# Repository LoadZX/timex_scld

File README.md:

# Timex SCLD

This is an implementation of the Timex TC2068 SCLD as can be found in Timex models TC2048 and TC2068.

# License

All the design files (VHDL code, PCB designs) are licensed under a Creative Commons Attribution-ShareAlike 4.0 International License.

You should have received a copy of the license along with this work. If not, see <https://creativecommons.org/licenses/by-sa/4.0/>.

A copy of the legal license text is placed in this repository (see LICENSE)

# Trademarks

TIMEX is a trademark of TIMEX GROUP USA, INC

The authors of this work are not affiliated, sponsored or have any partnership with the trademark holders. The trademark holders do not sponsor or endorse this work or any of its authors.

Xilinx is a registered trademark of Xilinx in the United States and other countries.

# Implementation code
The implementation (VHDL code and associated files) target a XC95144XL-10TQ100 CPLD from Xilinx. 

## Synthesis
The tool used for synthesis and fitting was Xilinx ISE 14.7. 

## Programming
Programming can be acomplished with Xilinx Impact using a proper programmer (i.e., Xilinx Platform Cable)

# Building

Just type "make" under the SDLC implementation folder (syn/xilinx). Alternatively you can try loading the ISE project in the same directory.

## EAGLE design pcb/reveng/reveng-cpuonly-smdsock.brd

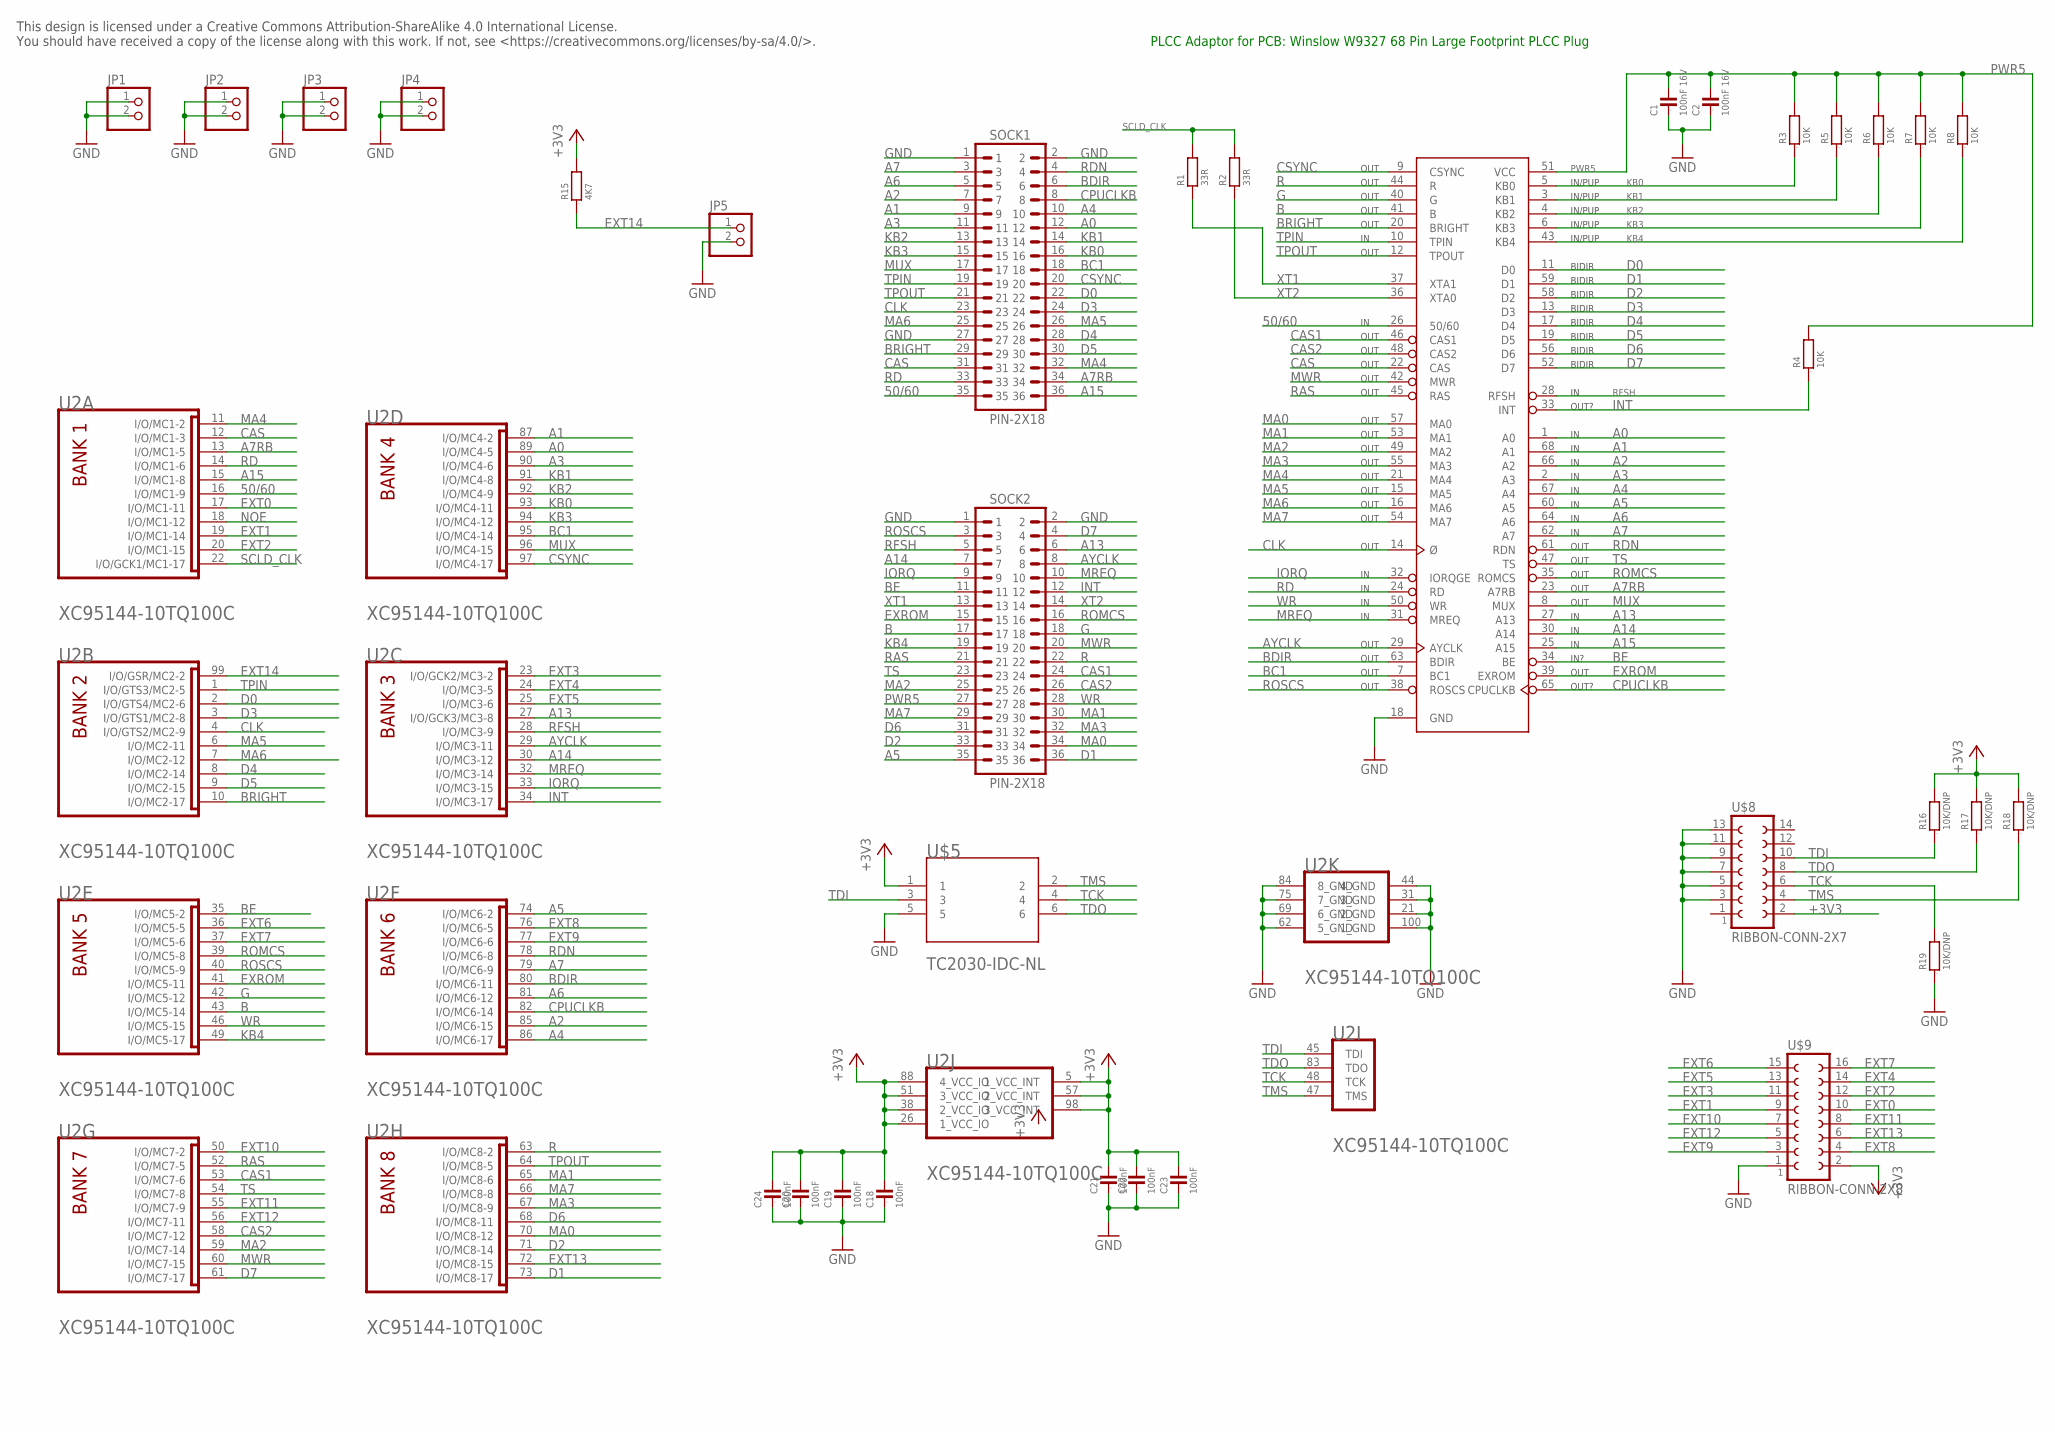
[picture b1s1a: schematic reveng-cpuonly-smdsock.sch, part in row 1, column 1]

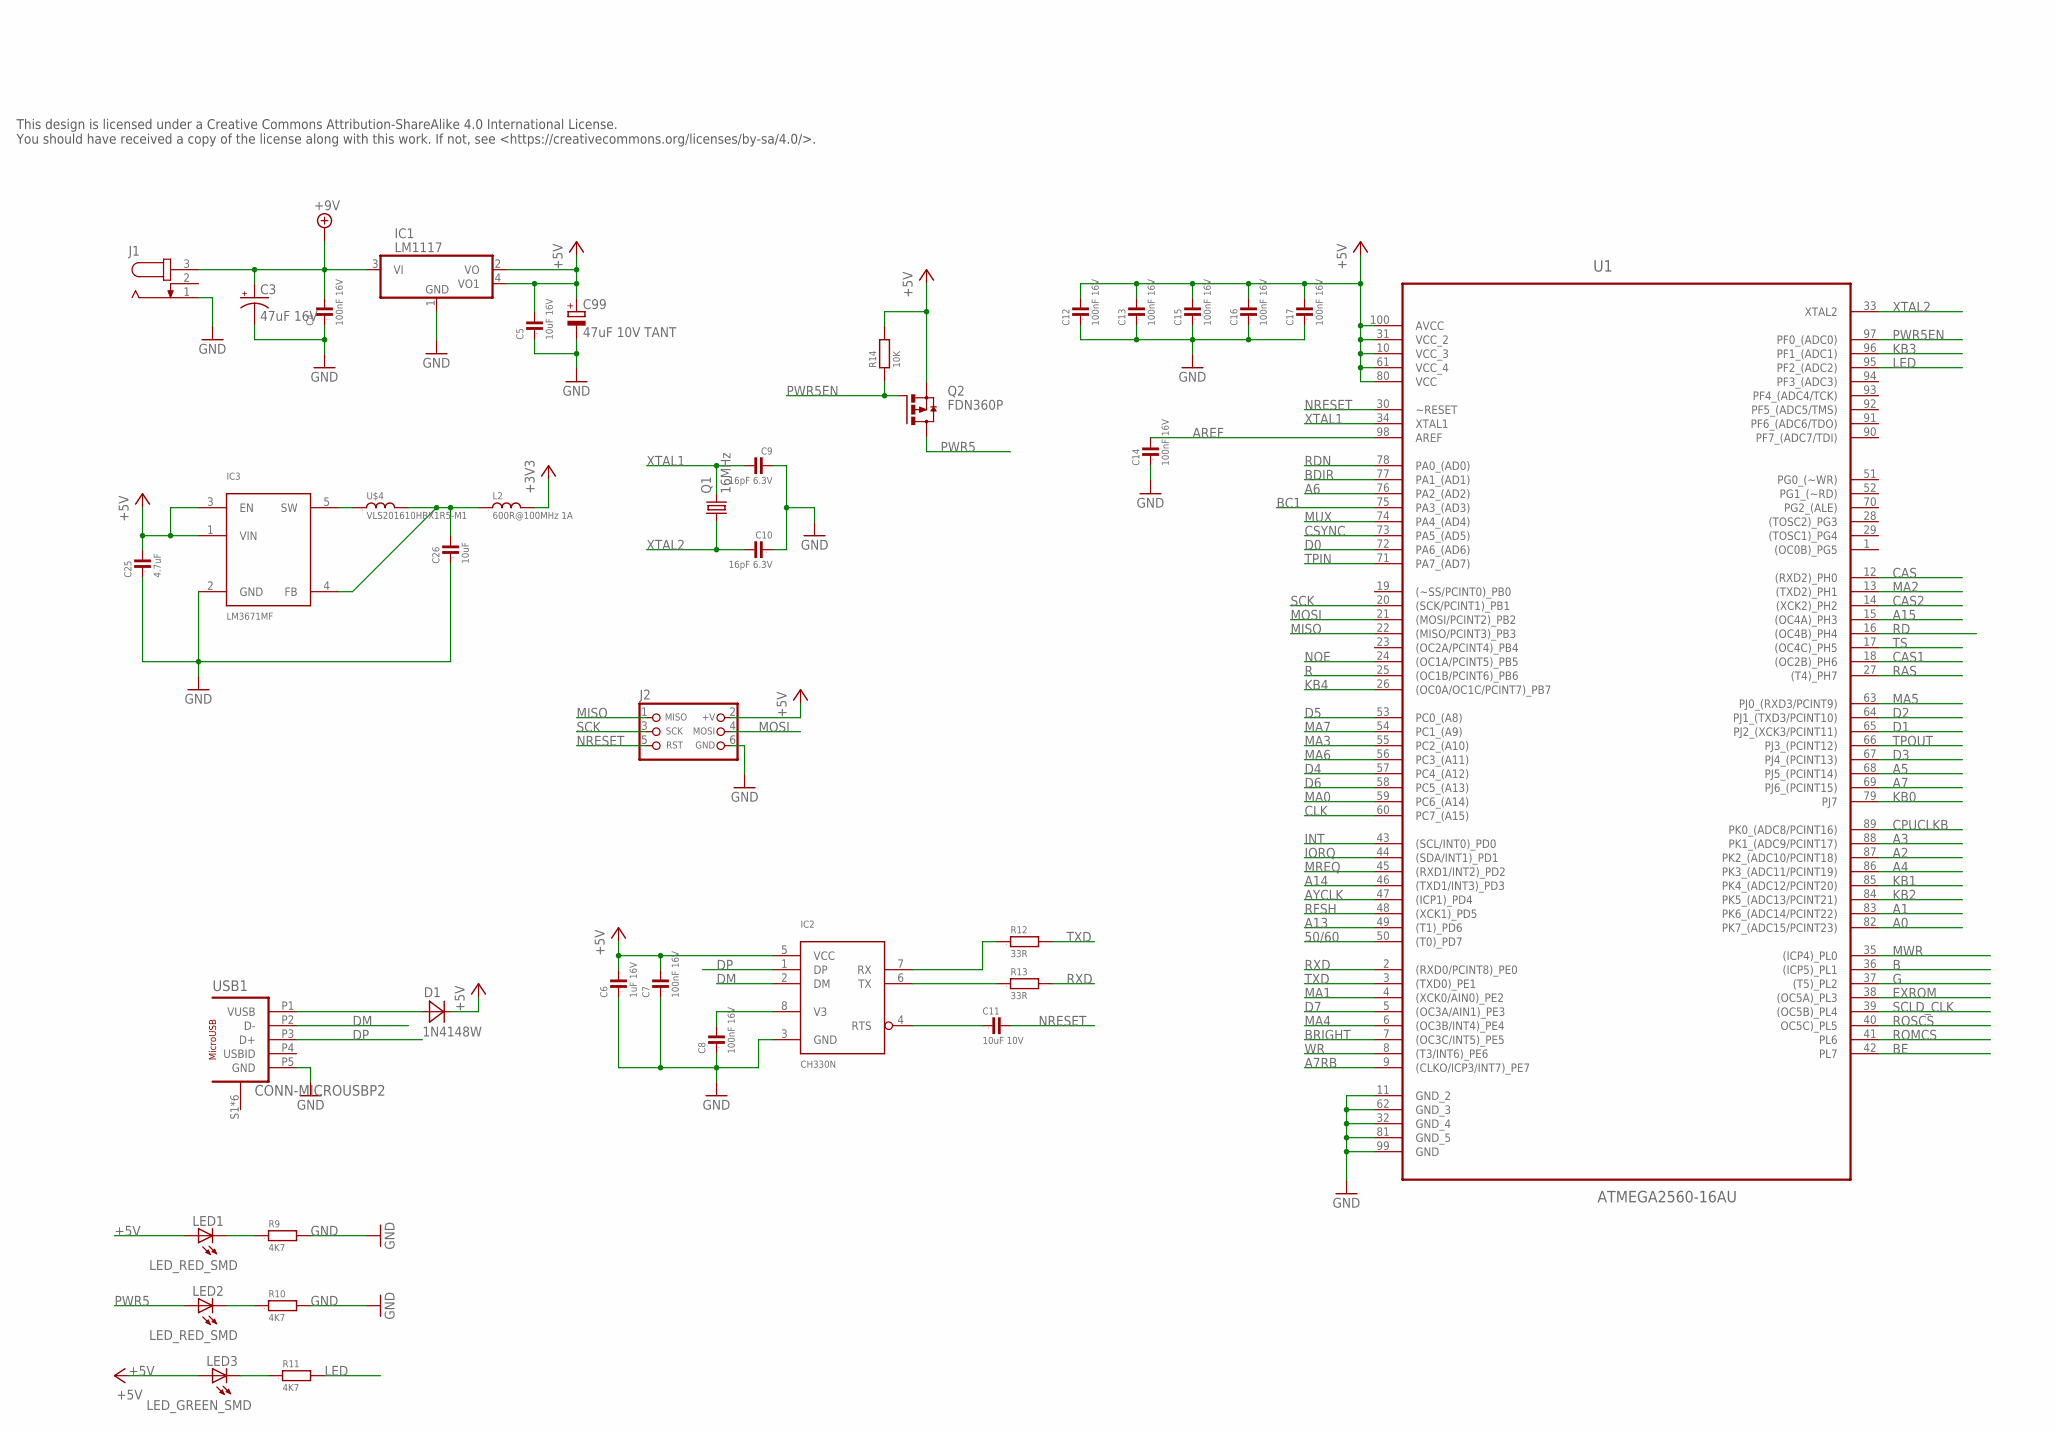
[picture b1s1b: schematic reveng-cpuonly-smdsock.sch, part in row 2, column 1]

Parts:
C1, C2, C4, C7, C8, C12, C13, C14, C15, C16, C17: 100nF 16V; 0603
C3: 47uF 16V; E2,5-6
C5: 10uF 16V; 0805
C6: 1uF 16V; 0603
C9, C10: 16pF 6.3V; 0603
C11: 10uF 10V; 0603
C18, C19, C20, C21, C22, C23, C24: 100nF; 0603
C25: 4.7uF; 0805
C26: 10uF; 0805
C99: 47uF 10V TANT; TANT_CASE_A
D1: 1N4148W; SOD-123
IC1: LM1117; SOT223
IC2: CH330N; SOIC8
IC3: LM3671MF; SOT23-5L
J1: JACK-PLUG; SPC4078-NOSLOT
J2: CON_HEADER_PRG_AVR_ICSP-PTH; HEADER_PRG_2X03
JP1, JP2, JP3, JP4, JP5: PINHD-1X2; 1X02
L2: 600R@100MHz 1A; 0805
LED1, LED2: LED_RED_SMD; LED-603
LED3: LED_GREEN_SMD; LED-603
Q1: 16MHz; HC49U-V
Q2: FDN360P; SUPER-SOT3
R1, R2, R12, R13: 33R; 0603
R3, R4, R5, R6, R7, R8, R14: 10K; 0603
R9, R10, R11, R15: 4K7; 0603
R16, R17, R18, R19: 10K/DNP; 0603
SCLD1: 2048SCLDSMDSOCK; PLCC68-AMP-SOCKET
SOCK1, SOCK2: PIN-2X18
U1: ATMEGA2560-16AU; QFP50P1600X1600X120-100N
U2: XILINX_XC95144-10TQ100CLQFP; LQFP100
U$4: VLS201610HBX1R5-M1; IND_0806
U$5: TC2030-IDC-NL
U$8: RIBBON-CONN-2X7
U$9: RIBBON-CONN-2X8
USB1: CONN-MICROUSBP2; MICROUSB_SMD_TH_7.5MM_4.85MM

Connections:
50/60: SCLD1.26 (50/60), SOCK1.35, U1.50 ((T0)_PD7), U2.16 (I/O/MC1-9)
+3V3: C18.2, C19.2, C20.2, C21.2, C22.2, C23.2, C24.2, L2.2, R15.2, R16.2, R17.2, R18.2, U2.5 (1_VCC_INT), U2.26 (1_VCC_IO), U2.38 (2_VCC_IO), U2.51 (3_VCC_IO), U2.57 (2_VCC_INT), U2.88 (4_VCC_IO), U2.98 (3_VCC_INT), U$5.1, U$8.2, U$9.2
+5V: C5.2, C6.2, C7.2, C12.2, C13.2, C15.2, C16.2, C17.2, C25.2, C99.PLUS (+), D1.1 (C), IC1.2 (VO), IC1.4 (VO1), IC2.5 (VCC), IC3.1 (VIN), IC3.3 (EN), J2.2 (+V), LED1.A, LED3.A, Q2.2 (S), R14.2, U1.10 (VCC_3), U1.31 (VCC_2), U1.61 (VCC_4), U1.80 (VCC), U1.100 (AVCC)
+9V: C3.+, C4.2, IC1.3 (VI), J1.3
A0: SCLD1.1 (A0), SOCK1.12, U1.82 (PK7_(ADC15/PCINT23)), U2.89 (I/O/MC4-5)
A1: SCLD1.68 (A1), SOCK1.9, U1.83 (PK6_(ADC14/PCINT22)), U2.87 (I/O/MC4-2)
A2: SCLD1.66 (A2), SOCK1.7, U1.87 (PK2_(ADC10/PCINT18)), U2.85 (I/O/MC6-15)
A3: SCLD1.2 (A3), SOCK1.11, U1.88 (PK1_(ADC9/PCINT17)), U2.90 (I/O/MC4-6)
A4: SCLD1.67 (A4), SOCK1.10, U1.86 (PK3_(ADC11/PCINT19)), U2.86 (I/O/MC6-17)
A5: SCLD1.60 (A5), SOCK2.35, U1.68 (PJ5_(PCINT14)), U2.74 (I/O/MC6-2)
A6: SCLD1.64 (A6), SOCK1.5, U1.76 (PA2_(AD2)), U2.81 (I/O/MC6-12)
A7: SCLD1.62 (A7), SOCK1.3, U1.69 (PJ6_(PCINT15)), U2.79 (I/O/MC6-9)
A7RB: SCLD1.23 (A7RB), SOCK1.34, U1.9 ((CLKO/ICP3/INT7)_PE7), U2.13 (I/O/MC1-5)
A13: SCLD1.27 (A13), SOCK2.6, U1.49 ((T1)_PD6), U2.27 (I/O/GCK3/MC3-8)
A14: SCLD1.30 (A14), SOCK2.7, U1.46 ((TXD1/INT3)_PD3), U2.30 (I/O/MC3-12)
A15: SCLD1.25 (A15), SOCK1.36, U1.15 ((OC4A)_PH3), U2.15 (I/O/MC1-8)
AREF: C14.2, U1.98 (AREF)
AYCLK: SCLD1.29 (AYCLK), SOCK2.8, U1.47 ((ICP1)_PD4), U2.29 (I/O/MC3-11)
B: SCLD1.41 (B), SOCK2.17, U1.36 ((ICP5)_PL1), U2.43 (I/O/MC5-14)
BC1: SCLD1.7 (BC1), SOCK1.18, U1.75 (PA3_(AD3)), U2.95 (I/O/MC4-14)
BDIR: SCLD1.63 (BDIR), SOCK1.6, U1.77 (PA1_(AD1)), U2.80 (I/O/MC6-11)
BE: SCLD1.34 (BE), SOCK2.11, U1.42 (PL7), U2.35 (I/O/MC5-2)
BRIGHT: SCLD1.20 (BRIGHT), SOCK1.29, U1.7 ((OC3C/INT5)_PE5), U2.10 (I/O/MC2-17)
CAS: SCLD1.22 (CAS), SOCK1.31, U1.12 ((RXD2)_PH0), U2.12 (I/O/MC1-3)
CAS1: SCLD1.46 (CAS1), SOCK2.24, U1.18 ((OC2B)_PH6), U2.53 (I/O/MC7-6)
CAS2: SCLD1.48 (CAS2), SOCK2.26, U1.14 ((XCK2)_PH2), U2.58 (I/O/MC7-12)
CLK: SCLD1.14 (Ø), SOCK1.23, U1.60 (PC7_(A15)), U2.4 (I/O/GTS2/MC2-9)
CPUCLKB: SCLD1.65 (CPUCLKB), SOCK1.8, U1.89 (PK0_(ADC8/PCINT16)), U2.82 (I/O/MC6-14)
CSYNC: SCLD1.9 (CSYNC), SOCK1.20, U1.73 (PA5_(AD5)), U2.97 (I/O/MC4-17)
D0: SCLD1.11 (D0), SOCK1.22, U1.72 (PA6_(AD6)), U2.2 (I/O/GTS4/MC2-6)
D1: SCLD1.59 (D1), SOCK2.36, U1.65 (PJ2_(XCK3/PCINT11)), U2.73 (I/O/MC8-17)
D2: SCLD1.58 (D2), SOCK2.33, U1.64 (PJ1_(TXD3/PCINT10)), U2.71 (I/O/MC8-14)
D3: SCLD1.13 (D3), SOCK1.24, U1.67 (PJ4_(PCINT13)), U2.3 (I/O/GTS1/MC2-8)
D4: SCLD1.17 (D4), SOCK1.28, U1.57 (PC4_(A12)), U2.8 (I/O/MC2-14)
D5: SCLD1.19 (D5), SOCK1.30, U1.53 (PC0_(A8)), U2.9 (I/O/MC2-15)
D6: SCLD1.56 (D6), SOCK2.31, U1.58 (PC5_(A13)), U2.68 (I/O/MC8-11)
D7: SCLD1.52 (D7), SOCK2.4, U1.5 ((OC3A/AIN1)_PE3), U2.61 (I/O/MC7-17)
DM: IC2.2 (DM), USB1.P2 (D-)
DP: IC2.1 (DP), USB1.P3 (D+)
EXROM: SCLD1.39 (EXROM), SOCK2.15, U1.38 ((OC5A)_PL3), U2.41 (I/O/MC5-11)
EXT0: U2.17 (I/O/MC1-11), U$9.10
EXT1: U2.19 (I/O/MC1-14), U$9.9
EXT2: U2.20 (I/O/MC1-15), U$9.12
EXT3: U2.23 (I/O/GCK2/MC3-2), U$9.11
EXT4: U2.24 (I/O/MC3-5), U$9.14
EXT5: U2.25 (I/O/MC3-6), U$9.13
EXT6: U2.36 (I/O/MC5-5), U$9.15
EXT7: U2.37 (I/O/MC5-6), U$9.16
EXT8: U2.76 (I/O/MC6-5), U$9.4
EXT9: U2.77 (I/O/MC6-6), U$9.3
EXT10: U2.50 (I/O/MC7-2), U$9.7
EXT11: U2.55 (I/O/MC7-9), U$9.8
EXT12: U2.56 (I/O/MC7-11), U$9.5
EXT13: U2.72 (I/O/MC8-15), U$9.6
EXT14: JP5.1, R15.1, U2.99 (I/O/GSR/MC2-2)
G: SCLD1.40 (G), SOCK2.18, U1.37 ((T5)_PL2), U2.42 (I/O/MC5-12)
GND: C1.1, C2.1, C3.-, C4.1, C5.1, C6.1, C7.1, C8.1, C9.1, C10.1, C12.1, C13.1, C14.1, C15.1, C16.1, C17.1, C18.1, C19.1, C20.1, C21.1, C22.1, C23.1, C24.1, C25.1, C26.1, C99.MINUS (-), IC1.1 (GND), IC2.3 (GND), IC3.2 (GND), J1.1, J2.6 (GND), JP1.1, JP1.2, JP2.1, JP2.2, JP3.1, JP3.2, JP4.1, JP4.2, JP5.2, R9.2, R10.2, R19.1, SCLD1.18 (GND), SOCK1.1, SOCK1.2, SOCK1.27, SOCK2.1, SOCK2.2, U1.11 (GND_2), U1.32 (GND_4), U1.62 (GND_3), U1.81 (GND_5), U1.99 (GND), U2.21 (2_GND), U2.31 (3_GND), U2.44 (4_GND), U2.62 (5_GND), U2.69 (6_GND), U2.75 (7_GND), U2.84 (8_GND), U2.100 (1_GND), U$5.5, U$8.3, U$8.5, U$8.7, U$8.9, U$8.11, U$8.13, U$9.1, USB1.P5 (GND)
INT: R4.1, SCLD1.33 (INT), SOCK2.12, U1.43 ((SCL/INT0)_PD0), U2.34 (I/O/MC3-17)
IORQ: SCLD1.32 (IORQGE), SOCK2.9, U1.44 ((SDA/INT1)_PD1), U2.33 (I/O/MC3-15)
KB0: R3.1, SCLD1.5 (KB0), SOCK1.16, U1.79 (PJ7), U2.93 (I/O/MC4-11)
KB1: R5.1, SCLD1.3 (KB1), SOCK1.14, U1.85 (PK4_(ADC12/PCINT20)), U2.91 (I/O/MC4-8)
KB2: R6.1, SCLD1.4 (KB2), SOCK1.13, U1.84 (PK5_(ADC13/PCINT21)), U2.92 (I/O/MC4-9)
KB3: R7.1, SCLD1.6 (KB3), SOCK1.15, U1.96 (PF1_(ADC1)), U2.94 (I/O/MC4-12)
KB4: R8.1, SCLD1.43 (KB4), SOCK2.19, U1.26 ((OC0A/OC1C/PCINT7)_PB7), U2.49 (I/O/MC5-17)
LED: R11.2, U1.95 (PF2_(ADC2))
MA0: SCLD1.57 (MA0), SOCK2.34, U1.59 (PC6_(A14)), U2.70 (I/O/MC8-12)
MA1: SCLD1.53 (MA1), SOCK2.30, U1.4 ((XCK0/AIN0)_PE2), U2.65 (I/O/MC8-6)
MA2: SCLD1.49 (MA2), SOCK2.25, U1.13 ((TXD2)_PH1), U2.59 (I/O/MC7-14)
MA3: SCLD1.55 (MA3), SOCK2.32, U1.55 (PC2_(A10)), U2.67 (I/O/MC8-9)
MA4: SCLD1.21 (MA4), SOCK1.32, U1.6 ((OC3B/INT4)_PE4), U2.11 (I/O/MC1-2)
MA5: SCLD1.15 (MA5), SOCK1.26, U1.63 (PJ0_(RXD3/PCINT9)), U2.6 (I/O/MC2-11)
MA6: SCLD1.16 (MA6), SOCK1.25, U1.56 (PC3_(A11)), U2.7 (I/O/MC2-12)
MA7: SCLD1.54 (MA7), SOCK2.29, U1.54 (PC1_(A9)), U2.66 (I/O/MC8-8)
MISO: J2.1 (MISO), U1.22 ((MISO/PCINT3)_PB3)
MOSI: J2.4 (MOSI), U1.21 ((MOSI/PCINT2)_PB2)
MREQ: SCLD1.31 (MREQ), SOCK2.10, U1.45 ((RXD1/INT2)_PD2), U2.32 (I/O/MC3-14)
MUX: SCLD1.8 (MUX), SOCK1.17, U1.74 (PA4_(AD4)), U2.96 (I/O/MC4-15)
MWR: SCLD1.42 (MWR), SOCK2.20, U1.35 ((ICP4)_PL0), U2.60 (I/O/MC7-15)
unnamed: C8.2, IC2.8 (V3)
unnamed: D1.2 (A), USB1.P1 (VUSB)
unnamed: IC2.7 (RX), R12.1
unnamed: IC2.6 (TX), R13.1
unnamed: C11.1, IC2.4 (RTS)
unnamed: LED2.C, R10.1
unnamed: LED3.C, R11.1
unnamed: LED1.C, R9.1
NOE: U1.24 ((OC1A/PCINT5)_PB5), U2.18 (I/O/MC1-12)
NRESET: C11.2, J2.5 (RST), U1.30 (~RESET)
PWR5: C1.2, C2.2, LED2.A, Q2.3 (D), R3.2, R4.2, R5.2, R6.2, R7.2, R8.2, SCLD1.51 (VCC), SOCK2.27
PWR5EN: Q2.1 (G), R14.1, U1.97 (PF0_(ADC0))
R: SCLD1.44 (R), SOCK2.22, U1.25 ((OC1B/PCINT6)_PB6), U2.63 (I/O/MC8-2)
RAS: SCLD1.45 (RAS), SOCK2.21, U1.27 ((T4)_PH7), U2.52 (I/O/MC7-5)
RD: SCLD1.24 (RD), SOCK1.33, U1.16 ((OC4B)_PH4), U2.14 (I/O/MC1-6)
RDN: SCLD1.61 (RDN), SOCK1.4, U1.78 (PA0_(AD0)), U2.78 (I/O/MC6-8)
RFSH: SCLD1.28 (RFSH), SOCK2.5, U1.48 ((XCK1)_PD5), U2.28 (I/O/MC3-9)
ROMCS: SCLD1.35 (ROMCS), SOCK2.16, U1.41 (PL6), U2.39 (I/O/MC5-8)
ROSCS: SCLD1.38 (ROSCS), SOCK2.3, U1.40 (OC5C)_PL5), U2.40 (I/O/MC5-9)
RXD: R13.2, U1.2 ((RXD0/PCINT8)_PE0)
SCK: J2.3 (SCK), U1.20 ((SCK/PCINT1)_PB1)
SCLD_CLK: R1.2, R2.2, U1.39 ((OC5B)_PL4), U2.22 (I/O/GCK1/MC1-17)
SW: IC3.5 (SW), U$4.P$1 (1)
TCK: R19.2, U2.48 (TCK), U$5.4, U$8.6
TDI: R16.1, U2.45 (TDI), U$5.3, U$8.10
TDO: R17.1, U2.83 (TDO), U$5.6, U$8.8
TMS: R18.1, U2.47 (TMS), U$5.2, U$8.4
TPIN: SCLD1.10 (TPIN), SOCK1.19, U1.71 (PA7_(AD7)), U2.1 (I/O/GTS3/MC2-5)
TPOUT: SCLD1.12 (TPOUT), SOCK1.21, U1.66 (PJ3_(PCINT12)), U2.64 (I/O/MC8-5)
TS: SCLD1.47 (TS), SOCK2.23, U1.17 ((OC4C)_PH5), U2.54 (I/O/MC7-8)
TXD: R12.2, U1.3 ((TXD0)_PE1)
V33: C26.2, IC3.4 (FB), L2.1, U$4.P$2 (2)
WR: SCLD1.50 (WR), SOCK2.28, U1.8 ((T3/INT6)_PE6), U2.46 (I/O/MC5-15)
XT1: R1.1, SCLD1.37 (XTA1), SOCK2.13
XT2: R2.1, SCLD1.36 (XTA0), SOCK2.14
XTAL1: C9.2, Q1.2, U1.34 (XTAL1)
XTAL2: C10.2, Q1.1, U1.33 (XTAL2)

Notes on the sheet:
BIDIR
OUT
OUT?
IN/PUP
IN?
PLCC Adaptor for PCB: Winslow W9327 68 Pin Large Footprint PLCC Plug
This design is licensed under a Creative Commons Attribution-ShareAlike 4.0 International License. You should have received a copy of the license along with this work. If not, see <https://creativecommons.org/licenses/by-sa/4.0/>.

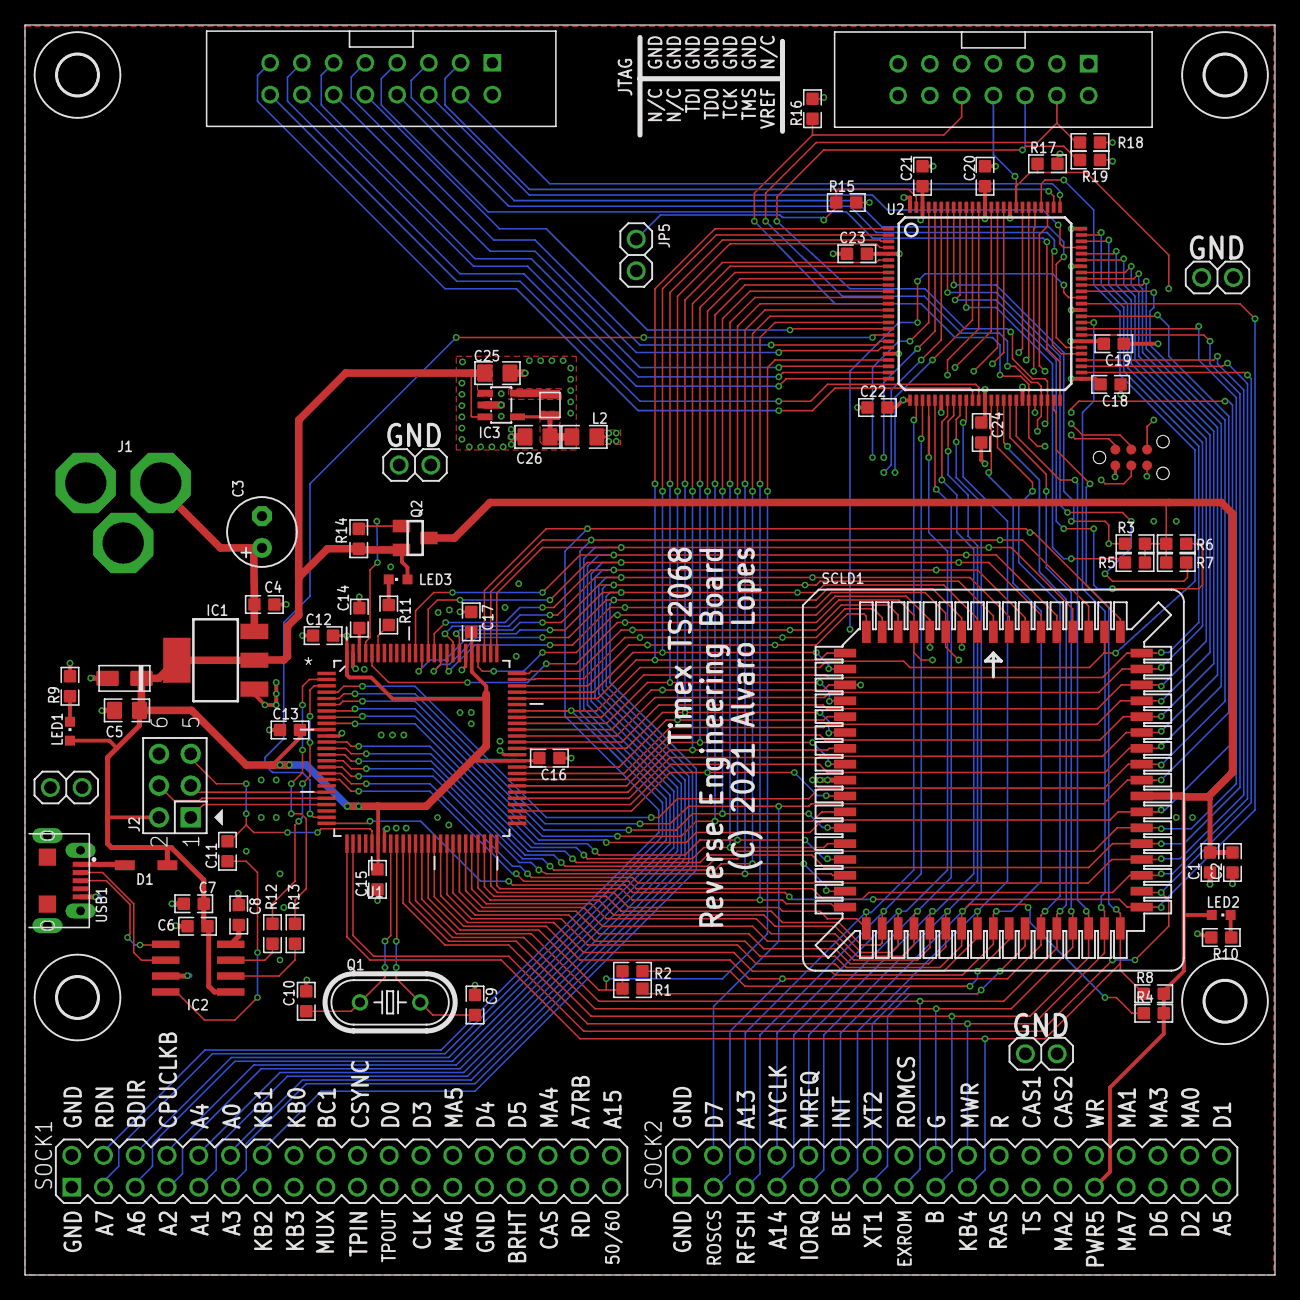
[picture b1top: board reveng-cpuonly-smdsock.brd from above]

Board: 4 copper layers, 100.0 x 100.0 mm, 77 parts (0 on the bottom side), 115 nets.

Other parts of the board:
U$6, U$7, U$10, U$11: 3,2

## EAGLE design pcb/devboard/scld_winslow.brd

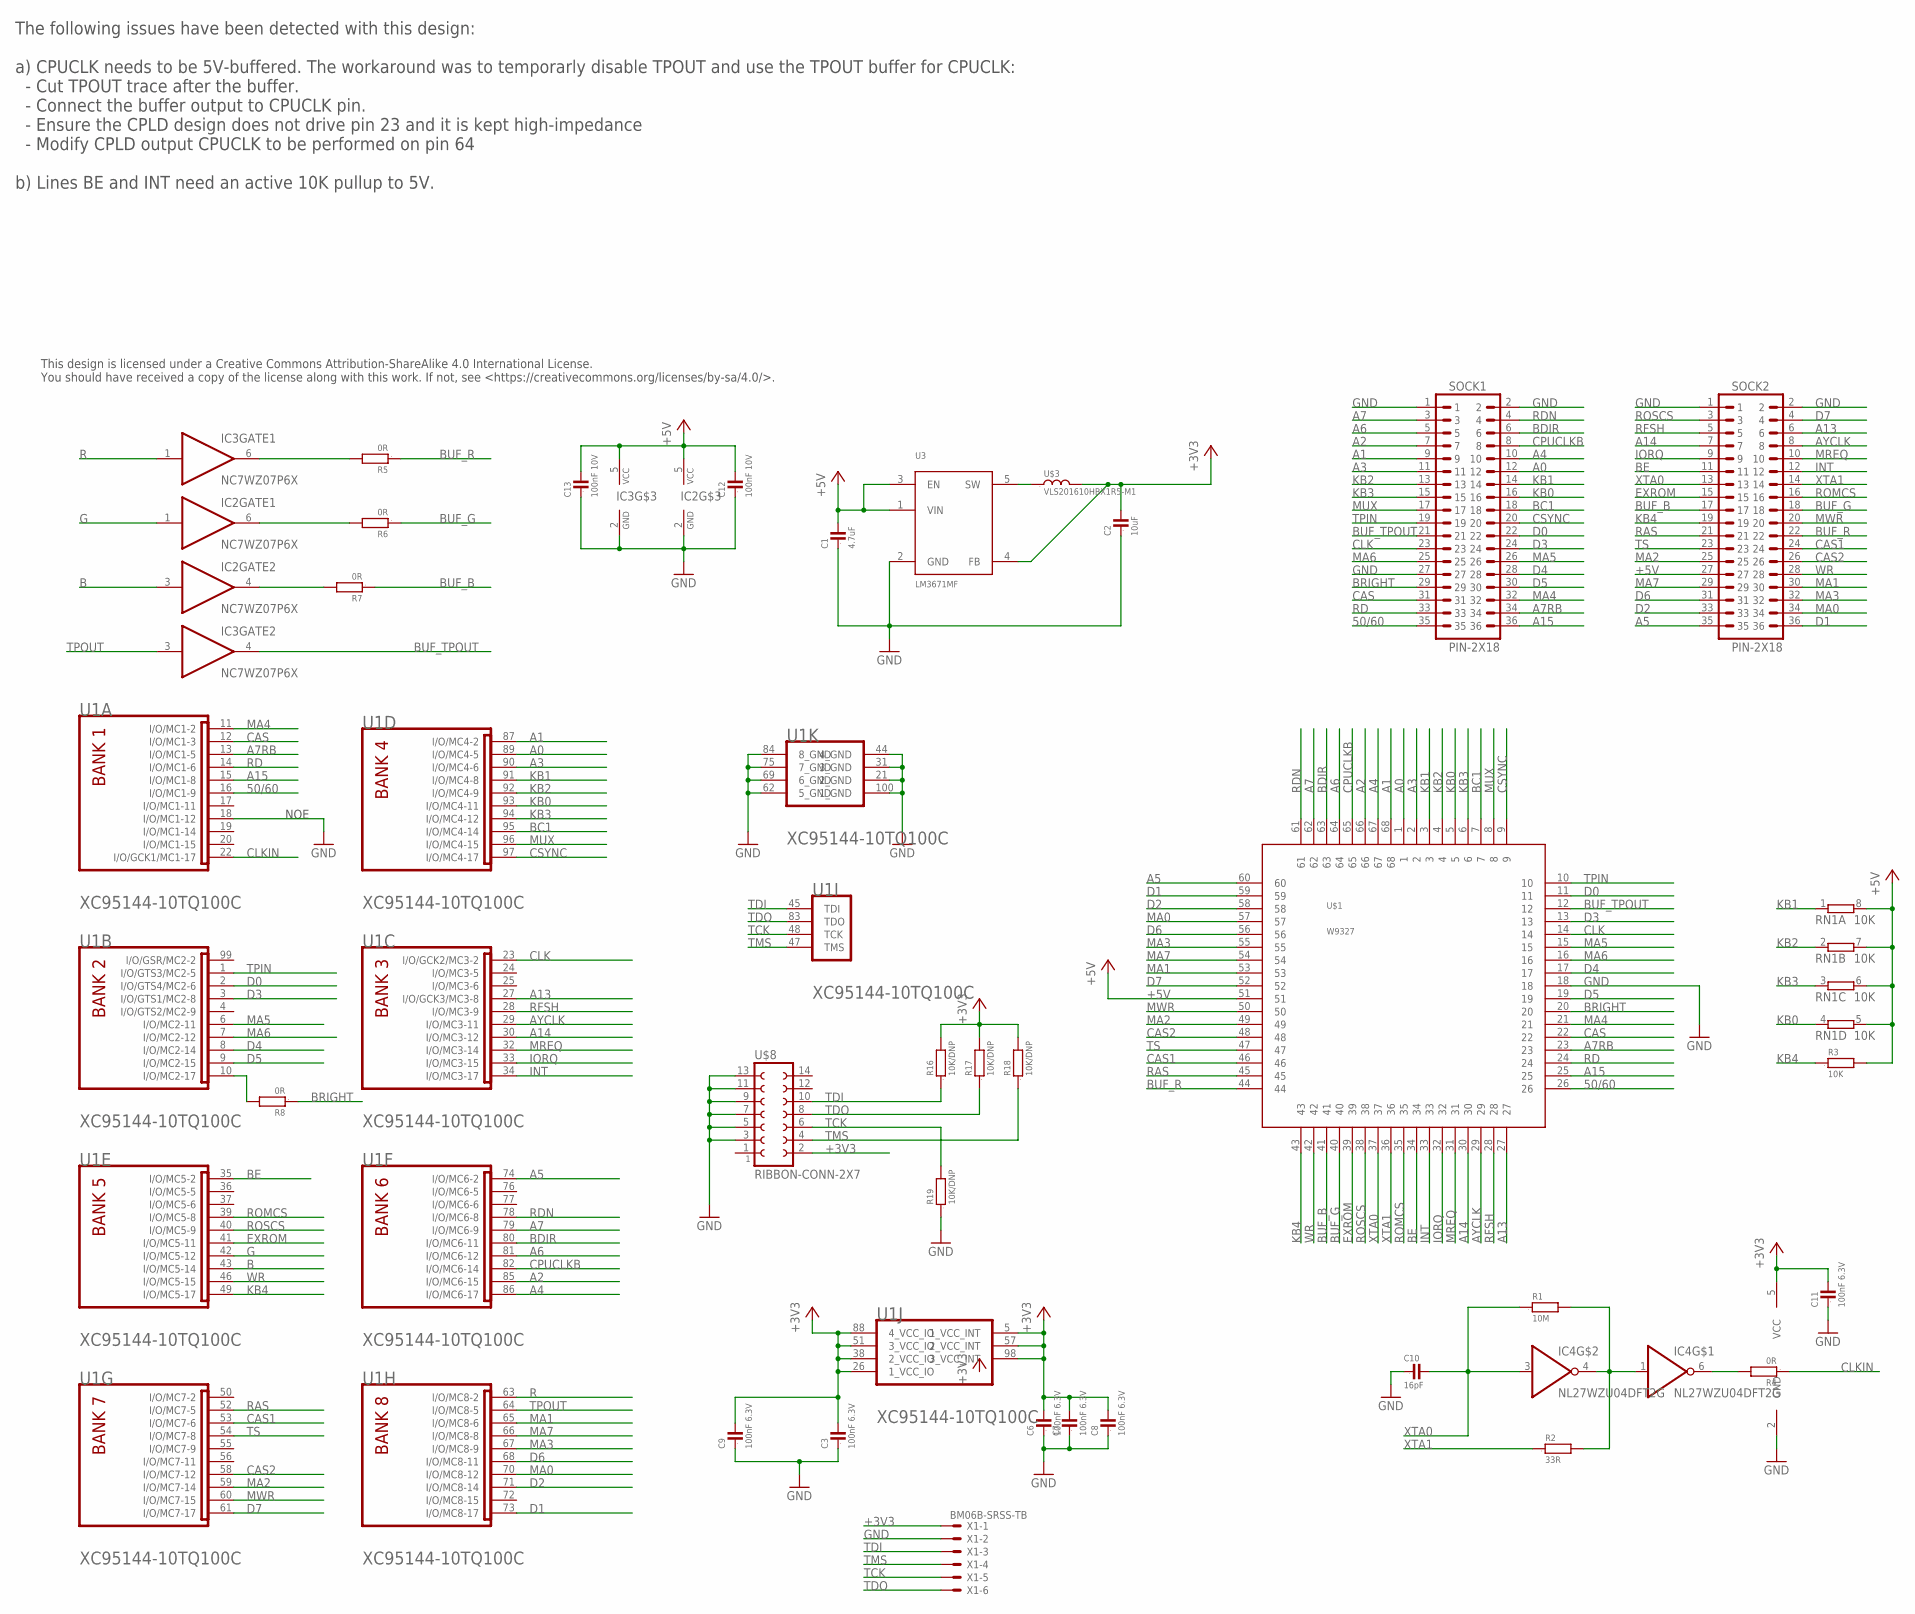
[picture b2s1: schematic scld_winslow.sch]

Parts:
C1: 4.7uF; 0805
C2: 10uF; 0805
C3, C6, C7, C8, C9, C11: 100nF 6.3V; 0402
C10: 16pF; 0402
C12, C13: 100nF 10V; 0402
IC2, IC3: NC7WZ07P6X; SC70-6
IC4: NL27WZU04DFT2G; SC70-6
R1: 10M; 0402
R2: 33R; 0402
R3: 10K; 0402
R4, R5, R6, R7, R8: 0R; 0603
R16, R17, R18, R19: 10K/DNP; 0603
RN1: 10K; EXB28V
SOCK1, SOCK2: PIN-2X18
U1: XILINX_XC95144-10TQ100CLQFP; LQFP100
U3: LM3671MF; SOT23-5L
U$1: W9327
U$3: VLS201610HBX1R5-M1; IND_0806
U$8: RIBBON-CONN-2X7
X1: BM06B-SRSS-TB

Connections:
50/60: SOCK1.35, U1.16 (I/O/MC1-9), U$1.26
+3V3: C2.2, C3.2, C6.2, C7.2, C8.2, C9.2, C11.2, IC4.5 (VCC), R16.2, R17.2, R18.2, U1.5 (1_VCC_INT), U1.26 (1_VCC_IO), U1.38 (2_VCC_IO), U1.51 (3_VCC_IO), U1.57 (2_VCC_INT), U1.88 (4_VCC_IO), U1.98 (3_VCC_INT), U3.4 (FB), U$3.P$2 (2), U$8.2, X1.1
+5V: C1.2, C12.2, C13.2, IC2.5 (VCC), IC3.5 (VCC), R3.2, RN1.5 (2), RN1.6 (2), RN1.7 (2), RN1.8 (2), SOCK2.27, U3.1 (VIN), U3.3 (EN), U$1.51
A0: SOCK1.12, U1.89 (I/O/MC4-5), U$1.1
A1: SOCK1.9, U1.87 (I/O/MC4-2), U$1.68
A2: SOCK1.7, U1.85 (I/O/MC6-15), U$1.66
A3: SOCK1.11, U1.90 (I/O/MC4-6), U$1.2
A4: SOCK1.10, U1.86 (I/O/MC6-17), U$1.67
A5: SOCK2.35, U1.74 (I/O/MC6-2), U$1.60
A6: SOCK1.5, U1.81 (I/O/MC6-12), U$1.64
A7: SOCK1.3, U1.79 (I/O/MC6-9), U$1.62
A7RB: SOCK1.34, U1.13 (I/O/MC1-5), U$1.23
A13: SOCK2.6, U1.27 (I/O/GCK3/MC3-8), U$1.27
A14: SOCK2.7, U1.30 (I/O/MC3-12), U$1.30
A15: SOCK1.36, U1.15 (I/O/MC1-8), U$1.25
AYCLK: SOCK2.8, U1.29 (I/O/MC3-11), U$1.29
B: IC2.3 (I), U1.43 (I/O/MC5-14)
BC1: SOCK1.18, U1.95 (I/O/MC4-14), U$1.7
BDIR: SOCK1.6, U1.80 (I/O/MC6-11), U$1.63
BE: SOCK2.11, U1.35 (I/O/MC5-2), U$1.34
BRIGHT: R8.1, SOCK1.29, U$1.20
BUF_B: R7.1, SOCK2.17, U$1.41
BUF_G: R6.1, SOCK2.18, U$1.40
BUF_R: R5.1, SOCK2.22, U$1.44
BUF_TPOUT: IC3.4 (O), SOCK1.21, U$1.12
CAS: SOCK1.31, U1.12 (I/O/MC1-3), U$1.22
CAS1: SOCK2.24, U1.53 (I/O/MC7-6), U$1.46
CAS2: SOCK2.26, U1.58 (I/O/MC7-12), U$1.48
CLK: SOCK1.23, U1.23 (I/O/GCK2/MC3-2), U$1.14
CLKIN: R4.1, U1.22 (I/O/GCK1/MC1-17)
CPUCLKB: SOCK1.8, U1.82 (I/O/MC6-14), U$1.65
CSYNC: SOCK1.20, U1.97 (I/O/MC4-17), U$1.9
D0: SOCK1.22, U1.2 (I/O/GTS4/MC2-6), U$1.11
D1: SOCK2.36, U1.73 (I/O/MC8-17), U$1.59
D2: SOCK2.33, U1.71 (I/O/MC8-14), U$1.58
D3: SOCK1.24, U1.3 (I/O/GTS1/MC2-8), U$1.13
D4: SOCK1.28, U1.8 (I/O/MC2-14), U$1.17
D5: SOCK1.30, U1.9 (I/O/MC2-15), U$1.19
D6: SOCK2.31, U1.68 (I/O/MC8-11), U$1.56
D7: SOCK2.4, U1.61 (I/O/MC7-17), U$1.52
EXROM: SOCK2.15, U1.41 (I/O/MC5-11), U$1.39
G: IC2.1 (I), U1.42 (I/O/MC5-12)
GND: C1.1, C2.1, C3.1, C6.1, C7.1, C8.1, C9.1, C10.1, C11.1, C12.1, C13.1, IC2.2 (GND), IC3.2 (GND), IC4.2 (GND), R19.1, SOCK1.1, SOCK1.2, SOCK1.27, SOCK2.1, SOCK2.2, U1.18 (I/O/MC1-12), U1.21 (2_GND), U1.31 (3_GND), U1.44 (4_GND), U1.62 (5_GND), U1.69 (6_GND), U1.75 (7_GND), U1.84 (8_GND), U1.100 (1_GND), U3.2 (GND), U$1.18, U$8.3, U$8.5, U$8.7, U$8.9, U$8.11, U$8.13, X1.2
INT: SOCK2.12, U1.34 (I/O/MC3-17), U$1.33
IORQ: SOCK2.9, U1.33 (I/O/MC3-15), U$1.32
KB0: RN1.4 (1), SOCK1.16, U1.93 (I/O/MC4-11), U$1.5
KB1: RN1.1, SOCK1.14, U1.91 (I/O/MC4-8), U$1.3
KB2: RN1.2 (1), SOCK1.13, U1.92 (I/O/MC4-9), U$1.4
KB3: RN1.3 (1), SOCK1.15, U1.94 (I/O/MC4-12), U$1.6
KB4: R3.1, SOCK2.19, U1.49 (I/O/MC5-17), U$1.43
MA0: SOCK2.34, U1.70 (I/O/MC8-12), U$1.57
MA1: SOCK2.30, U1.65 (I/O/MC8-6), U$1.53
MA2: SOCK2.25, U1.59 (I/O/MC7-14), U$1.49
MA3: SOCK2.32, U1.67 (I/O/MC8-9), U$1.55
MA4: SOCK1.32, U1.11 (I/O/MC1-2), U$1.21
MA5: SOCK1.26, U1.6 (I/O/MC2-11), U$1.15
MA6: SOCK1.25, U1.7 (I/O/MC2-12), U$1.16
MA7: SOCK2.29, U1.66 (I/O/MC8-8), U$1.54
MREQ: SOCK2.10, U1.32 (I/O/MC3-14), U$1.31
MUX: SOCK1.17, U1.96 (I/O/MC4-15), U$1.8
MWR: SOCK2.20, U1.60 (I/O/MC7-15), U$1.50
unnamed: IC4.6 (O), R4.2
unnamed: R8.2, U1.10 (I/O/MC2-17)
unnamed: IC3.6 (O), R5.2
unnamed: U3.5 (SW), U$3.P$1 (1)
unnamed: IC4.1 (I), IC4.4 (O), R1.2, R2.2
unnamed: IC2.4 (O), R7.2
unnamed: IC2.6 (O), R6.2
R: IC3.1 (I), U1.63 (I/O/MC8-2)
RAS: SOCK2.21, U1.52 (I/O/MC7-5), U$1.45
RD: SOCK1.33, U1.14 (I/O/MC1-6), U$1.24
RDN: SOCK1.4, U1.78 (I/O/MC6-8), U$1.61
RFSH: SOCK2.5, U1.28 (I/O/MC3-9), U$1.28
ROMCS: SOCK2.16, U1.39 (I/O/MC5-8), U$1.35
ROSCS: SOCK2.3, U1.40 (I/O/MC5-9), U$1.38
TCK: R19.2, U1.48 (TCK), U$8.6, X1.5
TDI: R16.1, U1.45 (TDI), U$8.10, X1.3
TDO: R17.1, U1.83 (TDO), U$8.8, X1.6
TMS: R18.1, U1.47 (TMS), U$8.4, X1.4
TPIN: SOCK1.19, U1.1 (I/O/GTS3/MC2-5), U$1.10
TPOUT: IC3.3 (I), U1.64 (I/O/MC8-5)
TS: SOCK2.23, U1.54 (I/O/MC7-8), U$1.47
WR: SOCK2.28, U1.46 (I/O/MC5-15), U$1.42
XTA0: C10.2, IC4.3 (I), R1.1, SOCK2.13, U$1.37
XTA1: R2.1, SOCK2.14, U$1.36

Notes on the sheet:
NOE
The following issues have been detected with this design: a) CPUCLK needs to be 5V-buffered. The workaround was to temporarly disable TPOUT and use the TPOUT buffer for CPUCLK: - Cut TPOUT trace after the buffer. - Connect the buffer output to CPUCLK pin. - Ensure the CPLD design does not drive pin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
This design is licensed under a Creative Commons Attribution-ShareAlike 4.0 International License. You should have received a copy of the license along with this work. If not, see <https://creativecommons.org/licenses/by-sa/4.0/>.

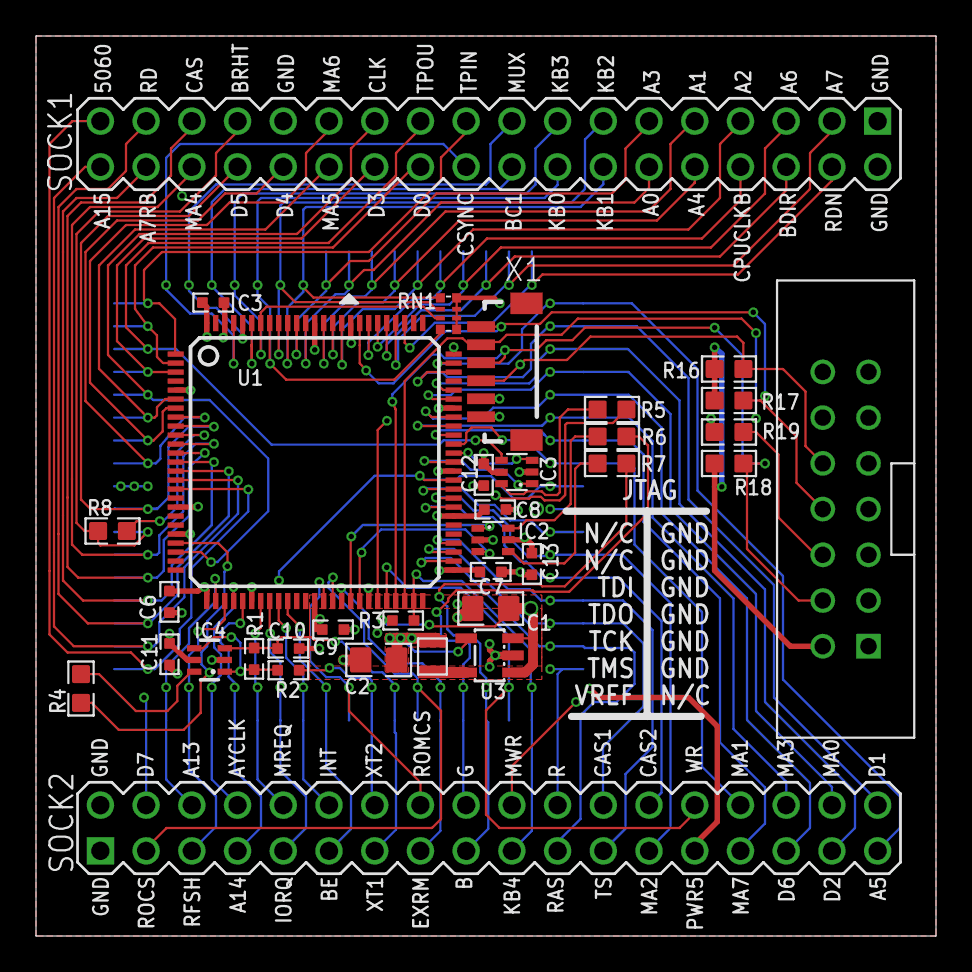
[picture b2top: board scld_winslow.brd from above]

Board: 4 copper layers, 50.0 x 50.0 mm, 35 parts (1 on the bottom side), 85 nets.

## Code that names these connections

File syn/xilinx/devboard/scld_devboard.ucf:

NET	"TPIN" 		LOC="1";
NET	"D<0>" 		LOC="2";
NET	"D<3>" 		LOC="3";
//NET	"CPUCLK"	LOC="4";
NET	"MA<5>"		LOC="6";
NET	"MA<6>"		LOC="7";
NET	"D<4>"		LOC="8";
NET	"D<5>"		LOC="9";
NET	"BRIGHT"	LOC="10";
NET	"MA<4>"		LOC = "11";
NET	"CAS" 		LOC = "12";
NET	"A7RB" 		LOC = "13";
NET	"RD" 		LOC = "14";
NET	"A<15>" 	LOC = "15";
NET	"P5060"		LOC = "16";
//NET	"NOE" 		LOC="18";
NET	"SCLD_CLK"	LOC = "22";
NET	"CPUCLK"	LOC = "23";
NET	"A<13>"		LOC = "27";
NET	"RFSH"		LOC = "28";
NET	"AYCLK"		LOC = "29";
NET	"A<14>"		LOC = "30";
NET	"MREQ"		LOC = "32";
NET	"IORQ"		LOC = "33";
NET	"INT"		LOC = "34";

NET	"BE"		LOC = "35";
NET	"ROMCS"		LOC = "39";
NET	"ROSCS"		LOC = "40";
NET	"EXROM"		LOC = "41";
NET	"G"		LOC = "42";
NET	"B"		LOC = "43";
NET	"WR"		LOC = "46";
NET	"KB<4>"		LOC = "49";

NET	"RAS"		LOC = "52";
NET	"CAS1"		LOC = "53";
NET	"TS"		LOC = "54";
NET	"CAS2"		LOC = "58";
NET	"MA<2>"		LOC = "59";
NET	"MWE"		LOC = "60";
NET	"D<7>"		LOC = "61";

NET	"R"		LOC = "63";
NET	"TPOUT"		LOC = "64";
NET	"MA<1>"		LOC = "65";
NET	"MA<7>"		LOC = "66";
NET	"MA<3>"		LOC = "67";
NET	"D<6>"		LOC = "68";
NET	"MA<0>"		LOC = "70";
NET	"D<2>"		LOC = "71";
NET	"D<1>"		LOC = "73";

NET	"A<5>"		LOC = "74";
NET	"RDN"		LOC = "78";
NET	"A<7>"		LOC = "79";
NET	"BDIR"		LOC = "80";
NET	"A<6>"		LOC = "81";
NET	"CPUCLKB"	LOC = "82";
NET	"A<2>"		LOC = "85";
NET	"A<4>"		LOC = "86";

NET	"A<1>"		LOC = "87";
NET	"A<0>"		LOC = "89";
NET	"A<3>"		LOC = "90";
NET	"KB<1>"		LOC = "91";
NET	"KB<2>"		LOC = "92";
NET	"KB<0>"		LOC = "93";
NET	"KB<3>"		LOC = "94";
NET	"BC1"		LOC = "95";
NET	"MUX"		LOC = "96";
NET	"CSYNC"		LOC = "97";

NET 	"SCLD_CLK" 	TNM_NET = SCLD_CLK;
TIMESPEC TS_SCLD_CLK = PERIOD "SCLD_CLK" 14 MHz HIGH 50%;

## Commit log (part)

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2023-11-11 Intial import of TIMEX SCLD CPLD implementation, reverse engineering board and development board.
2023-12-24 Correction: FLASH is indeed supported

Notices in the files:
pcb/devboard/scld_winslow.brd:
(C) 2022 Alvaro Lopes
pcb/reveng/reveng-cpuonly-smdsock.brd:
(C) 2021 Alvaro Lopes
